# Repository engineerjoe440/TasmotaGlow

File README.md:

# TasmotaGlow

*ESP-01S based controller built with Tasmota firmware in mind for shadow box lights.*

## BOM

| **Component ID** | **Description** | **Link** |
|------------------|-----------------|----------|
| PS1 | Mean Well IRM-10-12 | [DigiKey](https://www.digikey.com/en/products/detail/mean-well-usa-inc/IRM-10-12/7704653) |
| Q1 | ONSEMI BUZ11 TO-220 NMOS | [DigiKey](https://www.digikey.com/en/products/detail/onsemi/BUZ11-NR4941/1954150) |
| Q2 | ONSEMI BUZ11 TO-220 NMOS | [DigiKey](https://www.digikey.com/en/products/detail/onsemi/BUZ11-NR4941/1954150) |
| | Enclosure | [Amazon](https://a.co/d/7UIW7LF) |

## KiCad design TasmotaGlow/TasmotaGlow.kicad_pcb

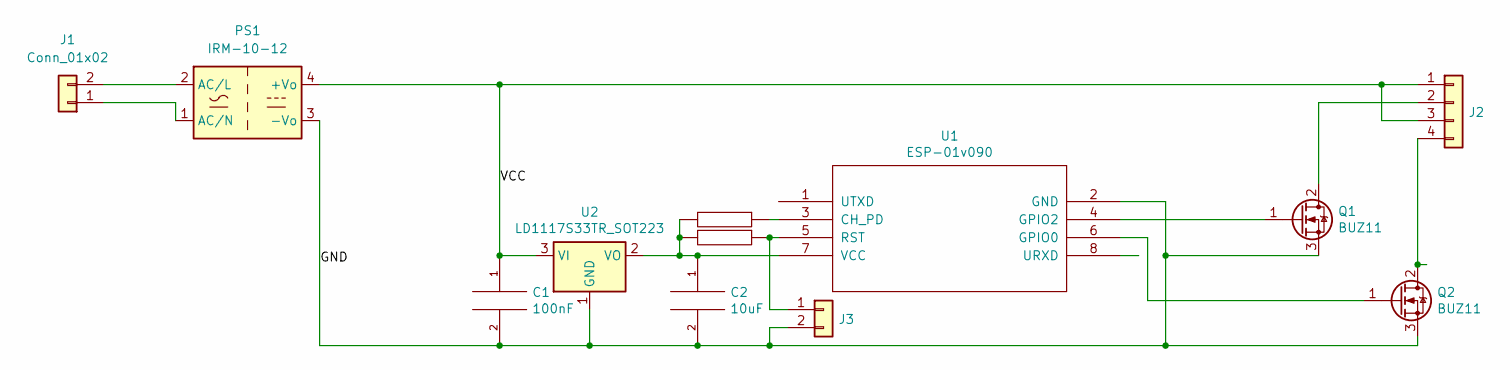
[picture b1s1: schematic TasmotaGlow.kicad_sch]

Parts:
C1: 100nF; C_Disc_D8.0mm_W5.0mm_P5.00mm
C2: 10uF; C_Disc_D8.0mm_W5.0mm_P5.00mm
J1: Conn_01x02; PhoenixContact_MCV_1,5_2-G-5.08_1x02_P5.08mm_Vertical
J2: Conn_01x04; PhoenixContact_MCV_1,5_4-G-5.08_1x04_P5.08mm_Vertical
J3: ResetPinout; PhoenixContact_MCV_1,5_2-G-5.08_1x02_P5.08mm_Vertical
PS1: IRM-10-12; Converter_ACDC_MeanWell_IRM-10-xx_THT
Q1, Q2: BUZ11; TO-220F-3_Vertical
R1, R2: 4.7k; R_Axial_DIN0207_L6.3mm_D2.5mm_P10.16mm_Horizontal
U1: ESP-01v090; ESP-01
U2: LD1117S33TR_SOT223; TO-220F-3_Vertical

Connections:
/GND: C1.2, C2.2, J3.2, PS1.3 (-Vo), Q1.3 (S), Q2.3 (S), U1.2 (GND), U2.1 (GND)
/VCC: C1.1, J2.1, J2.3, PS1.4 (+Vo), U2.3 (VI)
unnamed: J1.1, PS1.1 (AC/N)
unnamed: J1.2, PS1.2 (AC/L)
unnamed: J2.2, Q1.2 (D)
unnamed: J2.4, Q2.2 (D)
unnamed: J3.1, R2.1, U1.5 (RST)
unnamed: Q1.1 (G), U1.4 (GPIO2)
unnamed: Q2.1 (G), U1.6 (GPIO0)
unnamed: R1.1, U1.3 (CH_PD)
unnamed: C2.1, R1.2, R2.2, U1.7 (VCC), U2.2 (VO)

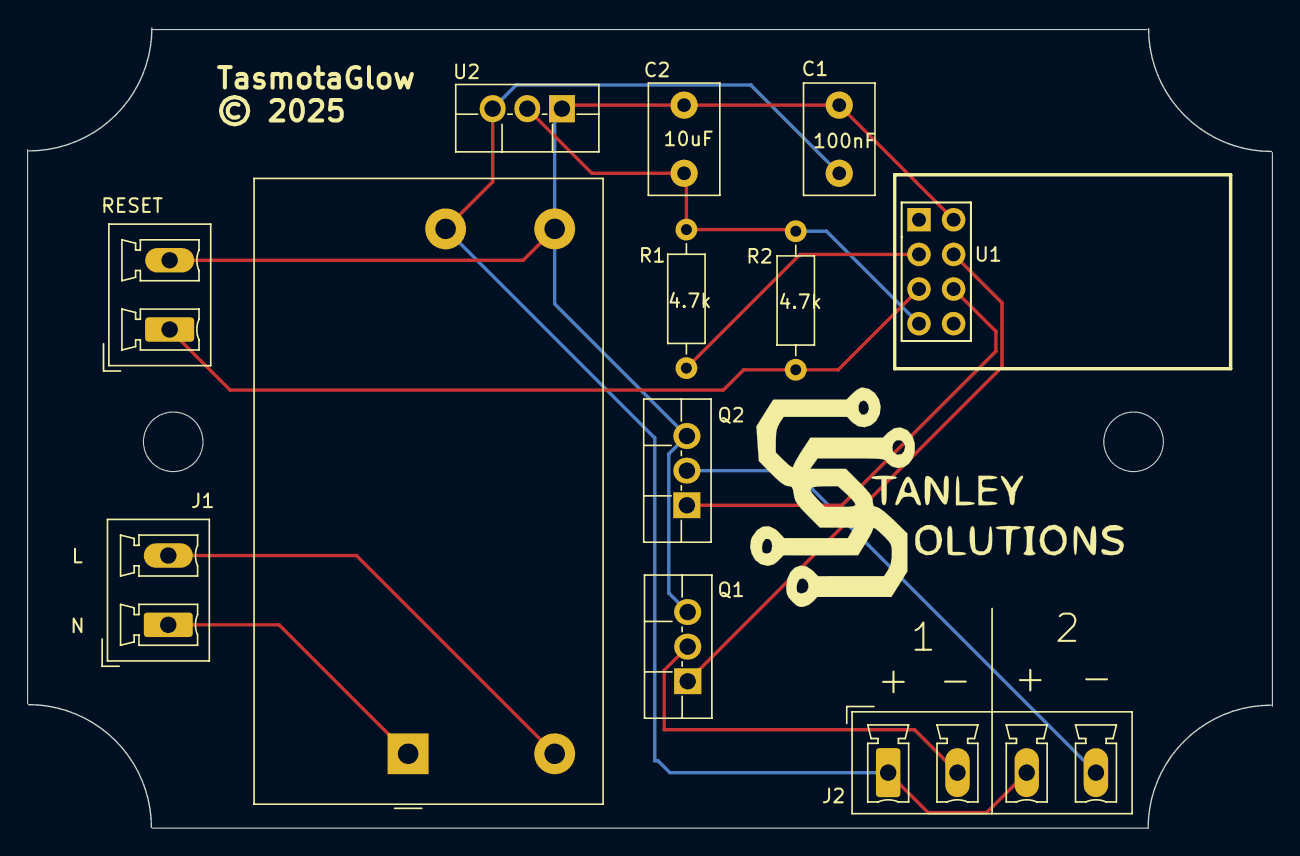
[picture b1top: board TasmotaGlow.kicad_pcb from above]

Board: 2 copper layers, 91.3 x 58.7 mm, 12 parts (0 on the bottom side), 11 nets.

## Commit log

2025-11-27 initial project setup
2025-11-27 updated circuit
2025-11-27 link to enclosure

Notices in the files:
TasmotaGlow/TasmotaGlow.kicad_pcb:
© 2025
TasmotaGlow/TasmotaGlow.kicad_sch:
License: GPLv3.0
